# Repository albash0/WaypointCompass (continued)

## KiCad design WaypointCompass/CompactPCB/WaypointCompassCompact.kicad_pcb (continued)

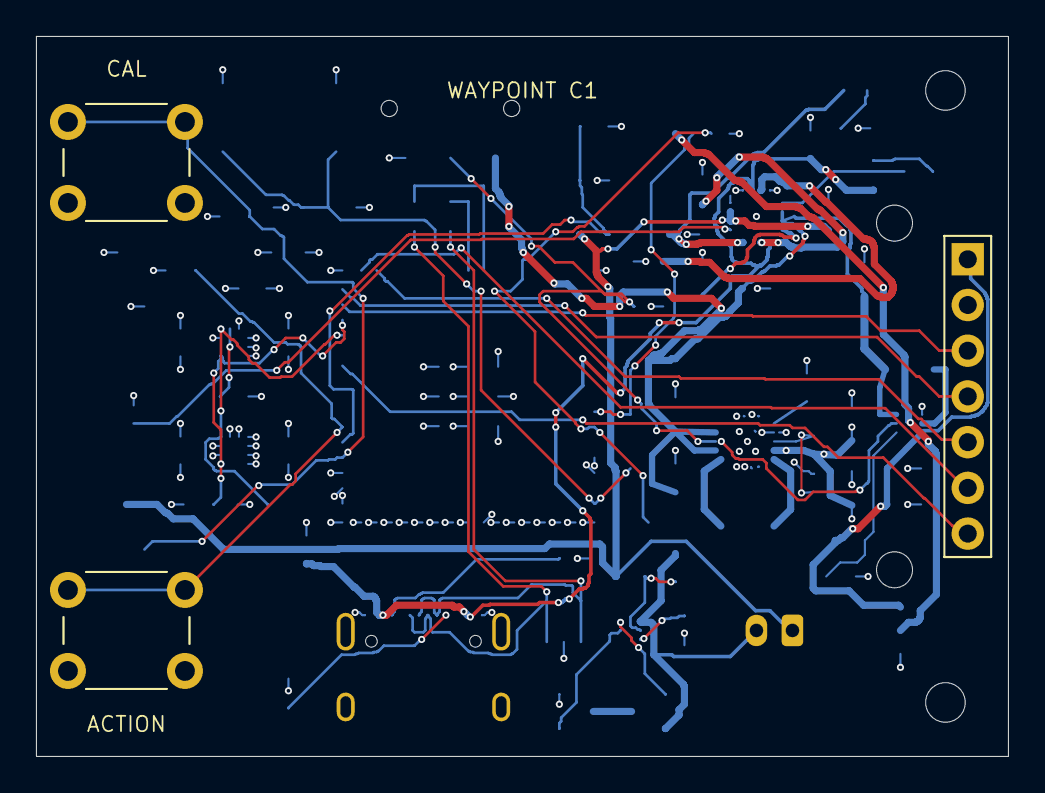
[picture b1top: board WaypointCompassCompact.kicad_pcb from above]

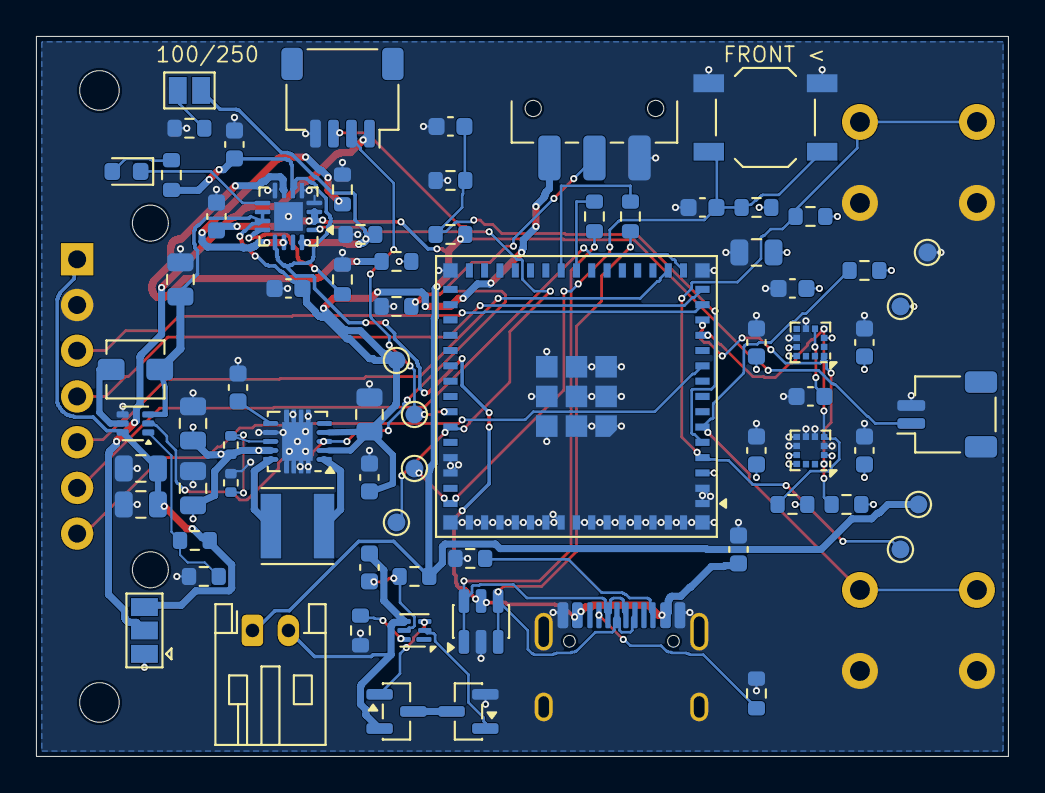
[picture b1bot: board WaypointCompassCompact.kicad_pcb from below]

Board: 4 copper layers, 54.0 x 40.0 mm, 82 parts (75 on the bottom side), 48 nets.

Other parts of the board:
H1, H2, H3, H4: MOUNT

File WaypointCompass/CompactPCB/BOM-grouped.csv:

References,Quantity,MPN,Value,Footprint,Assembly,Notes
U1,1,ESP32-S3-MINI-1U-N4R2,ESP32-S3-MINI-1U-N4R2,RF_Module:ESP32-S2-MINI-1U,Rear SMT,Optional external 2.4 GHz antenna; no RF used by compass firmware
U2,1,LIS2DH12TR,LIS2DH12TR,Package_LGA:LGA-12_2x2mm_P0.5mm,Rear SMT,I2C 0x18; +X must be mapped to device front
U3,1,LIS2MDLTR,LIS2MDLTR,Package_LGA:LGA-12_2x2mm_P0.5mm,Rear SMT,I2C 0x1E; NC pins 2/11/12 left open
U4,1,BQ24074RGTR,BQ24074RGTR,Package_DFN_QFN:VQFN-16-1EP_3x3mm_P0.5mm_EP1.6x1.6mm,Rear SMT,4.2 V single-cell; fixed 500 mA USB input mode; 100 mA default charge
U5,1,TPS63060DSCR,TPS63060DSCR,Package_SON:Texas_S-PWSON-N10,Rear SMT,3.3 V buck-boost; forced PWM for predictable sensor noise
U6,1,TPS61023DRLR,TPS61023DRLR,Package_TO_SOT_SMD:SOT-563,Rear SMT,5 V GPS breakout supply while running from battery
U7,1,BQ29700DSET,BQ29700DSET,Package_SON:WSON-6_1.5x1.5mm_P0.5mm,Rear SMT,4.275 V / 2.8 V cell protection; cell negative isolated from system GND
Q1,1,AO3400A,AO3400A,Package_TO_SOT_SMD:SOT-23,Rear SMT,Discharge FET; common drain with Q2
Q2,1,AO3400A,AO3400A,Package_TO_SOT_SMD:SOT-23,Rear SMT,Charge FET; common drain with Q1
U8,1,USBLC6-2SC6,USBLC6-2SC6,Package_TO_SOT_SMD:SOT-23-6,Rear SMT,USB ESD diode array placed near connector
J1,1,TYPE-C-31-M-12,USB-C USB2,Connector_USB:USB_C_Receptacle_HRO_TYPE-C-31-M-12,Rear SMT + shell through-hole,USB device; use a 5 V USB source capable of 500 mA
J2,1,Existing 7-pin GC9A01 TFT + straight 2.54 mm header,GC9A01 TFT,CompassCarrier:GC9A01_TFT_Socket,Front through-hole / manual,"Screen centered (27,20); 2.54 mm straight-header spacer; 5 V supply as on working prototype"
J3,1,S2B-PH-K-S(LF)(SN),BATTERY JST-PH2,Connector_JST:JST_PH_S2B-PH-K_1x02_P2.00mm_Horizontal,Rear through-hole,Pin 1 positive; 300-1000 mAh 1S 4.2 V-charge Li-ion/LiPo; verify plug polarity
J4,1,SM04B-SRSS-TB(LF)(SN),GPS JST-SH4,Connector_JST:JST_SH_SM04B-SRSS-TB_1x04-1MP_P1.00mm_Horizontal,Rear SMT,"New SH cable: VCC,RX,TX,GND; UART is 3.3 V"
J5,1,SM02B-SRSS-TB(LF)(SN),BATTERY NTC,Connector_JST:JST_SH_SM02B-SRSS-TB_1x02-1MP_P1.00mm_Horizontal,Rear SMT,External 10k 103AT-2 thermistor attached to cell; no NTC = charge inhibited
SW1,1,B3F-1000,CAL/BOOT,Button_Switch_THT:SW_PUSH_6mm,Front through-hole / manual,"Body center (5,7); GPIO0 held on reset enters ROM bootloader"
SW2,1,B3F-1000,ACTION,Button_Switch_THT:SW_PUSH_6mm,Front through-hole / manual,"Body center (5,33); GPIO2"
SW3,1,TL3342F160QG,RESET,Button_Switch_SMD:SW_SPST_TL3342,Rear SMT,Rear reset button
SW4,1,JS102011SAQN,POWER,Button_Switch_SMD:SW_SPDT_CK_JS102011SAQN,Rear SMT,Off grounds regulator enable; charger stays active
"R1, R2",2,RC0603FR-074K7L,4.7k,Resistor_SMD:R_0603_1608Metric,Rear SMT,"1%, 0603; "
"C1, C3, C8, C9, C10, C15, C18, C22",8,GRM188R71C104KA01D,100n,Capacitor_SMD:C_0603_1608Metric,Rear SMT,"100 nF, 16 V, X7R, 0603"
"C2, C4, C6, C11",4,GRM188R71A105KA61D,1u,Capacitor_SMD:C_0603_1608Metric,Rear SMT,"1 uF, 10 V, X7R, 0603"
C5,1,GRM188R71C224KA01D,220n,Capacitor_SMD:C_0603_1608Metric,Rear SMT,"220 nF, 16 V, X7R, 0603"
"R3, R4, R5, R17",4,RC0603FR-0710KL,10k,Resistor_SMD:R_0603_1608Metric,Rear SMT,"1%, 0603; "
"C7, C14, C19",3,GRM21BR61A106KE19L,10u,Capacitor_SMD:C_0805_2012Metric,Rear SMT,"10 uF, 10 V, X5R, 0805"
"R6, R7",2,RC0603FR-0722RL,22,Resistor_SMD:R_0603_1608Metric,Rear SMT,"1%, 0603; "
"R8, R9",2,RC0603FR-075K1L,5.1k,Resistor_SMD:R_0603_1608Metric,Rear SMT,"1%, 0603; "
R10,1,RC0603FR-07330KL,330k,Resistor_SMD:R_0603_1608Metric,Rear SMT,"1%, 0603; "
"R11, R18, R22",3,RC0603FR-07100KL,100k,Resistor_SMD:R_0603_1608Metric,Rear SMT,"1%, 0603; "
R12,1,RC0603FR-078K87L,8.87k,Resistor_SMD:R_0603_1608Metric,Rear SMT,"1%, 0603; "
R13,1,RC0603FR-075K9L,5.90k,Resistor_SMD:R_0603_1608Metric,Rear SMT,"1%, 0603; "
R14,1,RC0603FR-073K16L,3.16k,Resistor_SMD:R_0603_1608Metric,Rear SMT,"1%, 0603; ILIM unused in fixed USB500 mode; populated for defined pin bias"
R15,1,RC0603FR-0771K5L,71.5k,Resistor_SMD:R_0603_1608Metric,Rear SMT,"1%, 0603; 9.53 h typical timer; 7.15-11.92 h factor limits; 1000 mAh use 250 mA mode"
"C12, C13",2,GRM188R61A475KE15D,4.7u,Capacitor_SMD:C_0603_1608Metric,Rear SMT,"4.7 uF, 10 V, X5R, 0603"
"R16, R24",2,RC0603FR-072K2L,2.2k,Resistor_SMD:R_0603_1608Metric,Rear SMT,"1%, 0603; "
D1,1,LTST-C190KFKT,CHARGE amber,LED_SMD:LED_0603_1608Metric,Rear SMT,Charge active / fault indicator
L1,1,IFSC1515AHER1R5M01,1.5uH >=3A,Inductor_SMD:L_Vishay_IFSC-1515AH_4x4x1.8mm,Rear SMT,Vishay shielded 1.5 uH; 3.60 A nominal saturation current; 4 x 4 mm
"C16, C17, C20, C21",4,C2012X5R1A226M125AB,22u,Capacitor_SMD:C_0805_2012Metric,Rear SMT,"22 uF, 10 V, X5R, 0805"
R19,1,RC0402FR-07560KL,560k,Resistor_SMD:R_0402_1005Metric,Rear SMT,"1%, 0402; "
R20,1,RC0402FR-07100KL,100k,Resistor_SMD:R_0402_1005Metric,Rear SMT,"1%, 0402; "
L2,1,IHLP1212BZEV1R0M01,1uH >=2A,Inductor_SMD:L_Vishay_IHLP-1212,Rear SMT,Vishay shielded 1 uH IHLP-1212BZ-01; 6.92 A typical saturation; 4.99 A typical thermal rating
R21,1,RC0603FR-07732KL,732k,Resistor_SMD:R_0603_1608Metric,Rear SMT,"1%, 0603; "
R23,1,RC0603FR-07330RL,330,Resistor_SMD:R_0603_1608Metric,Rear SMT,"1%, 0603; "

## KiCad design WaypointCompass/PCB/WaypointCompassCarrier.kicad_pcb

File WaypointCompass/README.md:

# Waypoint Compass / Bottle Radar

The ESP32 selects the closest of **19 retail liquor stores** from the City of Boulder's public liquor-license map, using the current GPS position. It runs offline: no Wi-Fi, account, phone or API key is needed.

## Screen

- Mint-and-gold arrow, rotating north/cardinal markers and a large distance readout.
- Store name and left/right turn cue; north-up fallback when neither magnetometer heading nor GPS course is available.
- Animated GPS radar while acquiring a fix. No target arrow is shown with a stale or missing fix.
- Animated bottle calibration screen and a "FOUND IT!" celebration within 25 m of the destination's map point.
- Detailed GPS reception page with satellite counts, RX rate, NMEA checksums, SNR and HDOP.

Distances are **straight-line**, not walking routes. The nearest candidate is reevaluated once per second, so the target can change as you move. Store coordinates are city GIS points, not surveyed entrances. The embedded list is a **2026-10-16 snapshot**; opening hours and live closures are not checked. Grocery beer/wine licenses and bars are excluded; the list uses the city's `Retail Liquor Store` class with `STATUS=1`.

## Firmware variants

- `WaypointCompass.ino`: the working SuperMini + QMC5883P GY-271 + MPU6050 GY-521 prototype. The TFT's CS is tied to GND and RST to 3V3, matching its existing running sketch. SCK=10, MOSI=11, DC=13; GPS RX=44/TX=43; I2C SDA=8/SCL=9. GY-271 remains on the GY-521 auxiliary I2C bus with bypass enabled.
- `CompactPCB/firmware/WaypointCompassCompact/WaypointCompassCompact.ino`: the C1 PCB with LIS2MDL/LIS2DH12 and TFT CS=12/RST=6. QSPI PSRAM enabled for its ESP32-S3-MINI-1U-N4R2.

Both variants use the same `BoulderStores.h`, `BottleNavigation.h` and `BottleUI.h`. Their sensor setup, pin configuration, tilt compensation and saved calibration stay specific to their hardware. Keep the copied headers synchronized when editing either firmware.

## Upload and controls

Use ESP32S3 Dev Module, ESP32 Arduino core 3.3.8, 4 MB flash, Hardware CDC/JTAG USB mode and USB CDC On Boot enabled. Install TinyGPSPlus, Adafruit GFX and Adafruit GC9A01A with their dependencies. The prototype does not require PSRAM; C1 uses QSPI PSRAM.

BOOT/CAL starts a 10-second calibration. Roll, pitch and turn the assembled device around all axes; accepted calibration survives resets. The C1 ACTION button toggles detailed diagnostics. Serial Monitor uses 115200 baud with newline endings:

| Command | Action |
| --- | --- |
| `NEAREST` | Enable automatic nearest-store mode; saved across resets. This is the default for the new firmware. |
| `STORES` | Print the embedded store names, addresses and coordinates. |
| `DETAILS` | Toggle the detailed GPS screen. |
| `STATUS` | Report navigation mode, selected store, GPS and sensor status. |
| `CAL` | Start 10-second 3D calibration. |
| `NMEA` | Print five seconds of raw GPS data. |
| `latitude,longitude` | Save a manual waypoint and switch to manual mode. |
| `CLEAR` | Clear the manual target and disable automatic mode. Use NEAREST to resume. |

The old manual waypoint is ignored while automatic mode is active; calibration is retained. Automatic target updates do not write GPS positions to flash.

## Store data and checks

[City liquor-license map](https://maps.bouldercolorado.gov/liquor-licenses/) is linked from the [City licensing page](https://bouldercolorado.gov/services/liquor-licenses). The exact query and records are stored in `data/boulder-stores.json`.

To refresh the list, run `python3 tools/update_store_list.py` with internet access. It queries the city GIS, rejects missing/out-of-area coordinates and regenerates the header in both sketch folders. Recompile and upload afterward. Review business names/status when refreshing.

`tests/run_tests.sh` checks nearest-store selection, missing/stale fixes and geographic distance edge cases under address/undefined-behavior sanitizers. It also renders eight screens with the actual Adafruit GFX implementation for visual inspection. `preview/` contains sample UI images, not live measurements.

Personal waypoints and device backups are excluded from the public source export. Both compiled manual destination defaults are unset (`NAN`). Public city-listed business coordinates remain in the offline dataset.

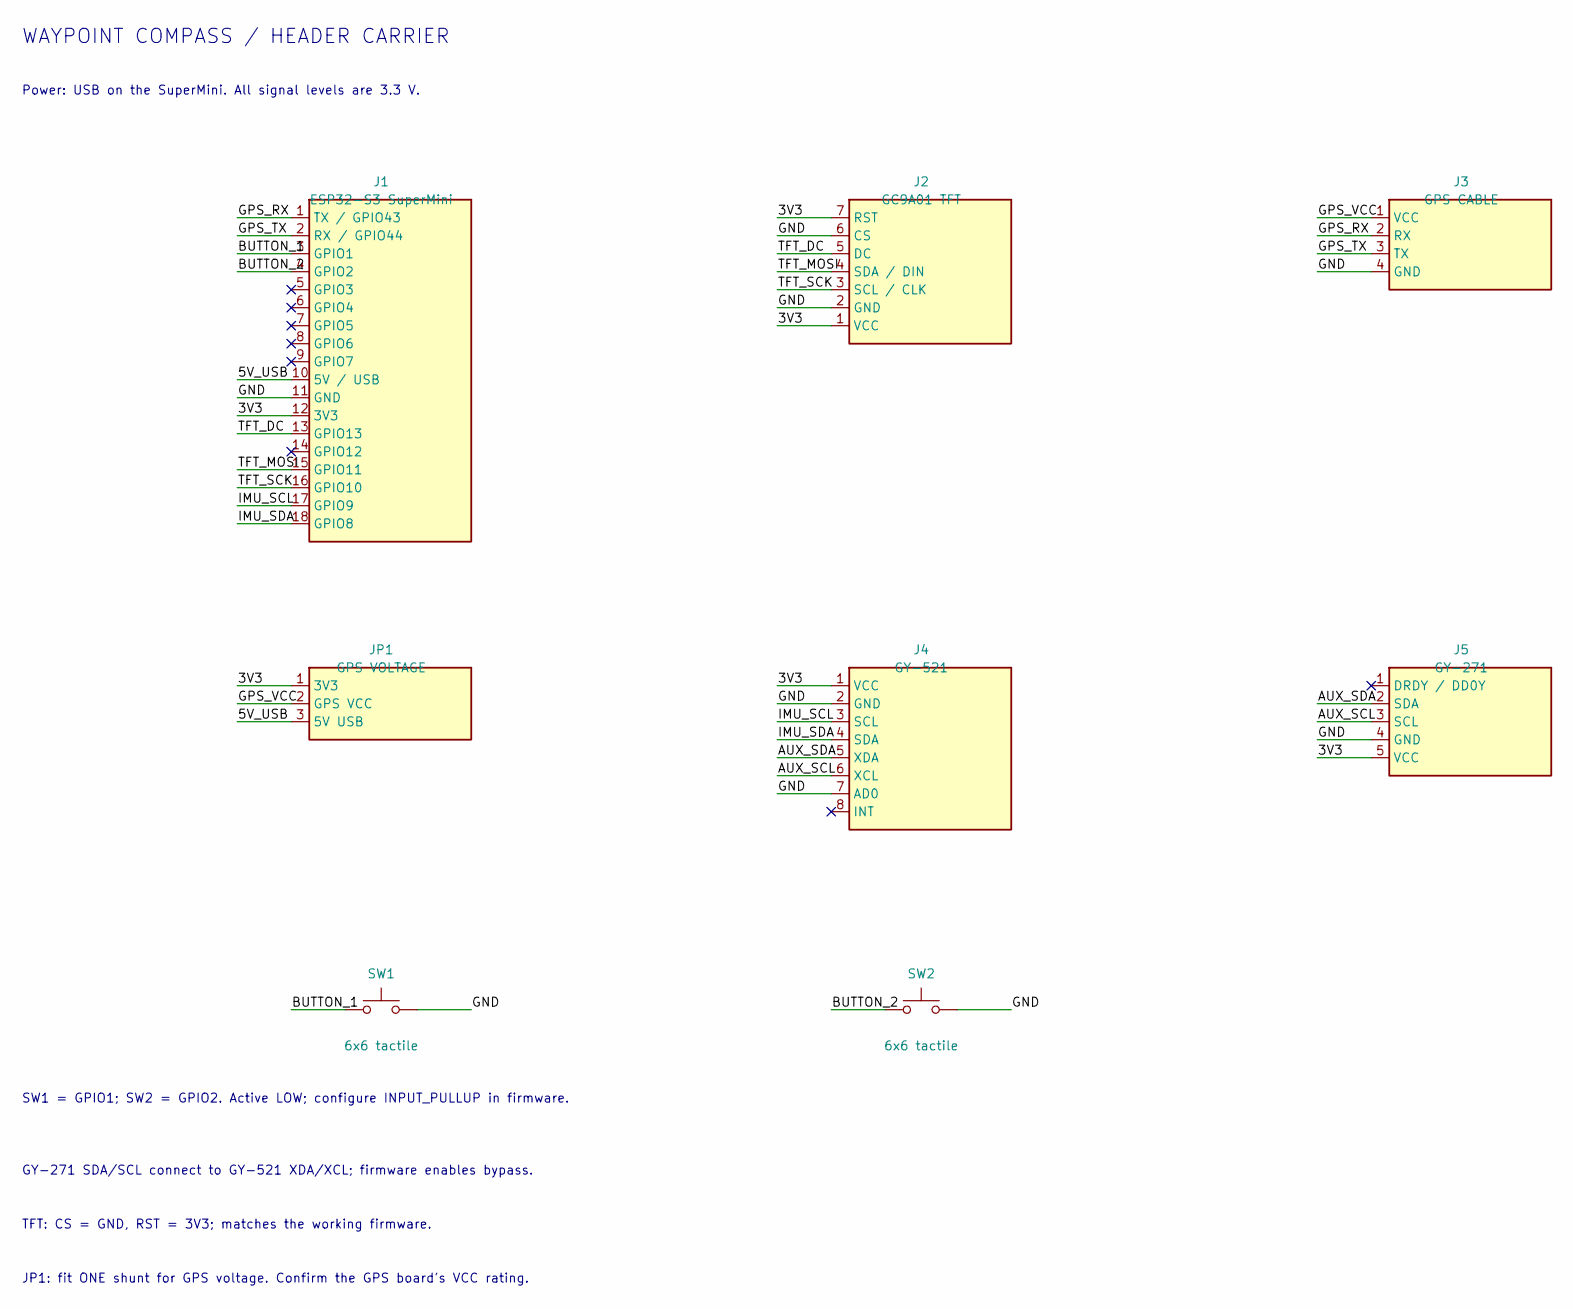
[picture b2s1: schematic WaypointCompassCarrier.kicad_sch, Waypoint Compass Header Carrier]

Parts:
J1: ESP32-S3 SuperMini; ESP32_S3_SuperMini_2x09_Sockets
J2: GC9A01 TFT; GC9A01_TFT_Socket
J3: GPS CABLE; GPS_CABLE_Socket
J4: GY-521; GY_521_Socket
J5: GY-271; GY_271_Socket
JP1: GPS VOLTAGE; GPS_VOLTAGE_Socket
SW1, SW2: 6x6 tactile; SW_PUSH_6mm

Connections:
/3V3: J1.12 (3V3), J2.1 (VCC), J2.7 (RST), J4.1 (VCC), J5.5 (VCC), JP1.1 (3V3)
/5V_USB: J1.10 (5V / USB), JP1.3 (5V USB)
/AUX_SCL: J4.6 (XCL), J5.3 (SCL)
/AUX_SDA: J4.5 (XDA), J5.2 (SDA)
/BUTTON_1: J1.3 (GPIO1), SW1.1
/BUTTON_2: J1.4 (GPIO2), SW2.1
/GND: J1.11 (GND), J2.2 (GND), J2.6 (CS), J3.4 (GND), J4.2 (GND), J4.7 (AD0), J5.4 (GND), SW1.2, SW2.2
/GPS_RX: J1.1 (TX / GPIO43), J3.2 (RX)
/GPS_TX: J1.2 (RX / GPIO44), J3.3 (TX)
/GPS_VCC: J3.1 (VCC), JP1.2 (GPS VCC)
/IMU_SCL: J1.17 (GPIO9), J4.3 (SCL)
/IMU_SDA: J1.18 (GPIO8), J4.4 (SDA)
/TFT_DC: J1.13 (GPIO13), J2.5 (DC)
/TFT_MOSI: J1.15 (GPIO11), J2.4 (SDA / DIN)
/TFT_SCK: J1.16 (GPIO10), J2.3 (SCL / CLK)

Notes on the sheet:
WAYPOINT COMPASS / HEADER CARRIER
Power: USB on the SuperMini. All signal levels are 3.3 V.
GY-271 SDA/SCL connect to GY-521 XDA/XCL; firmware enables bypass.
TFT: CS = GND, RST = 3V3; matches the working firmware.
JP1: fit ONE shunt for GPS voltage. Confirm the GPS board's VCC rating.
SW1 = GPIO1; SW2 = GPIO2. Active LOW; configure INPUT_PULLUP in firmware.

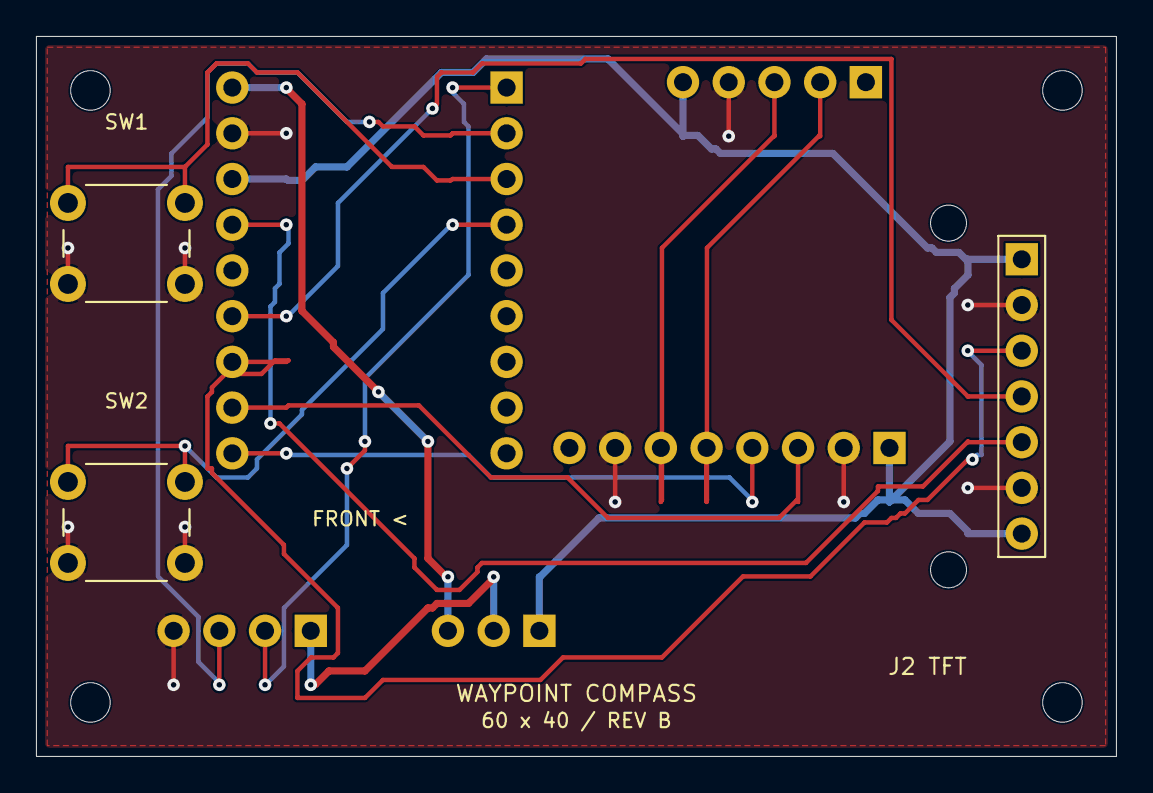
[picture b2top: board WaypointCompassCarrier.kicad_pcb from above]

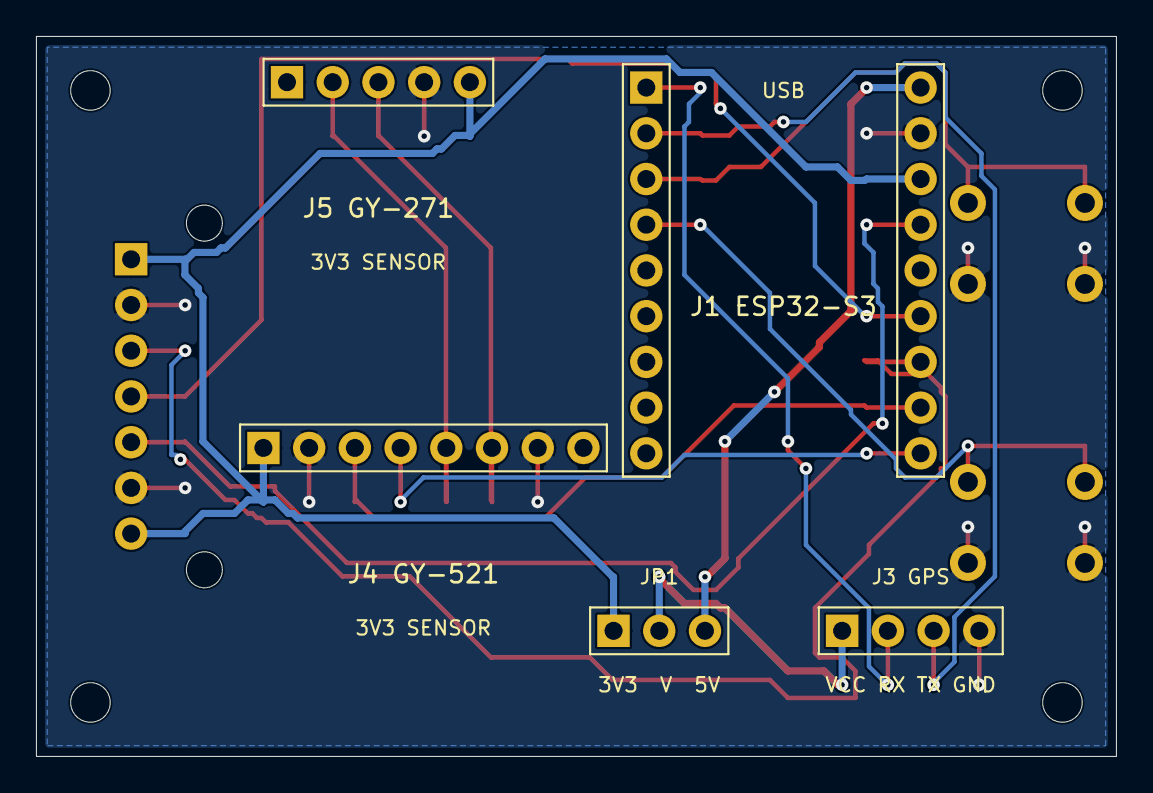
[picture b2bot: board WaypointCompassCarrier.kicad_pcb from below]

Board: 2 copper layers, 60.0 x 40.0 mm, 14 parts (5 on the bottom side), 15 nets.

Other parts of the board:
H1, H2, H3, H4: MountingHole_2.2mm; MountingHole_2.2mm_Carrier
H5, H6: MountingHole_2.0mm; MountingHole_2.0mm_Carrier

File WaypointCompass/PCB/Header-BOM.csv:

Reference,Quantity,Description,Pitch_mm,Side,Notes
J1,2,Male header 1x9 straight,2.54,Back,15.24 mm row spacing; solder to both boards; 2.54 mm PCB gap
J2,1,Male header 1x7 straight,2.54,Front,Direct solder; 2.54 mm gap; GC9A01 TFT; RST CS DC SDA SCL GND VCC
J3,1,Male header 1x4 straight,2.54,Back,GPS cable; VCC RX TX GND
J4,1,Male header 1x8 straight,2.54,Back,Direct solder; 2.54 mm gap; GY-521; VCC GND SCL SDA XDA XCL AD0 INT
J5,1,Male header 1x5 straight,2.54,Back,Direct solder; 2.54 mm gap; GY-271; DRDY SDA SCL GND VCC
JP1,1,Male header 1x3 straight,2.54,Back,GPS voltage selector
JP1,1,Jumper shunt 2-pin,2.54,Back,Select exactly one GPS supply
SW1 SW2,2,Standard 6x6 mm through-hole tactile pushbutton,,Front,Four leads on 6.50 x 4.50 mm spacing; normally open; short actuator
J3 cable,1,Four-wire female header cable,2.54,Off-board,Wire to GPS VCC RX TX GND
H1 H2 H3 H4,4,Optional M2 nonmagnetic case fasteners,,Both,2.20 mm carrier holes
H5 H6,2,Optional M1.6 nonmagnetic TFT supports,,Front,2.00 mm holes; 2.54 mm facing-PCB gap

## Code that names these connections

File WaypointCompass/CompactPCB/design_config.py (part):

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add('U1','ESP32-S3-MINI-1U-N4R2','RF_Module:ESP32-S3-MINI-1U','RF_Module:ESP32-S2-MINI-1U',mcu,[24,20],mpn='ESP32-S3-MINI-1U-N4R2',note='Optional external 2.4 GHz antenna; no RF used by compass firmware')
accel=custompins([(1,'SCL','input'),(2,'CS','input'),(3,'SA0','input'),(4,'SDA','bidirectional'),(5,'RES_GND','passive'),(6,'GND','power_in'),(7,'GND','passive'),(8,'GND','passive'),(9,'VDD','power_in'),(10,'VDD_IO','power_in'),(11,'INT2','output'),(12,'INT1','output')])
add('U2','LIS2DH12TR',None,'Package_LGA:LGA-12_2x2mm_P0.5mm',{1:'I2C_SCL',2:'3V3',3:'GND',4:'I2C_SDA',5:'GND',6:'GND',7:'GND',8:'GND',9:'3V3',10:'3V3'},[11,23],custom=accel,note='I2C 0x18; +X must be mapped to device front')
add('U3','LIS2MDLTR','Sensor_Magnetic:LIS2MDL','Package_LGA:LGA-12_2x2mm_P0.5mm',{1:'I2C_SCL',3:'3V3',4:'I2C_SDA',5:'MAG_C1',6:'GND',8:'GND',9:'3V3',10:'3V3'},[11,17],note='I2C 0x1E; NC pins 2/11/12 left open')
# Power path: VBUS -> charger -> SYS -> 3.3 V buck-boost / 5 V GPS boost.
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add('U5','TPS63060DSCR','Regulator_Switching:TPS63060','Package_SON:Texas_S-PWSON-N10',{1:'BB_L1',2:'SYS',3:'POWER_EN',4:'SYS',6:'BB_AUX',7:'GND',8:'BB_FB',9:'3V3',10:'BB_L2',11:'GND'},[41,20],note='3.3 V buck-boost; forced PWM for predictable sensor noise')
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add('Q1','AO3400A','Transistor_FET:AO3400A','Package_TO_SOT_SMD:SOT-23',{1:'PROT_DOUT',2:'CELL_NEG',3:'FET_MID'},[33,36],180,note='Discharge FET; common drain with Q2')
add('Q2','AO3400A','Transistor_FET:AO3400A','Package_TO_SOT_SMD:SOT-23',{1:'PROT_COUT',2:'GND',3:'FET_MID'},[29,36],note='Charge FET; common drain with Q1')
add('U8','USBLC6-2SC6','Power_Protection:USBLC6-2SC6','Package_TO_SOT_SMD:SOT-23-6',{1:'USB_M',2:'GND',3:'USB_P',4:'USB_P',5:'VBUS',6:'USB_M'},[20,31],note='USB ESD diode array placed near connector')
usb={p['number']:('GND' if p['name'] in ('GND','SHIELD') else 'VBUS' if p['name']=='VBUS' else 'USB_P' if p['name']=='D+' else 'USB_M' if p['name']=='D-' else p['name'] if p['name'] in ('CC1','CC2') else None) for p in pins(symbol('Connector','USB_C_Receptacle_USB2.0_16P'))}
add('J1','USB-C USB2','Connector:USB_C_Receptacle_USB2.0_16P','Connector_USB:USB_C_Receptacle_HRO_TYPE-C-31-M-12',usb,[20,38],note='USB device; use a 5 V USB source capable of 500 mA')
# Front TFT landing reused; keep the cheap existing display module.
tftp=custompins([(1,'VCC','power_in'),(2,'GND','power_in'),(3,'SCL','input'),(4,'SDA','input'),(5,'DC','input'),(6,'CS','input'),(7,'RST','input')])
add('J2','GC9A01 TFT',None,'CompassCarrier:GC9A01_TFT_Socket',{1:'GPS_5V',2:'GND',3:'TFT_SCK',4:'TFT_MOSI',5:'TFT_DC',6:'TFT_CS',7:'TFT_RST'},[51.74,20],90,'front',custom=tftp,note='Screen centered (27,20); 2.54 mm straight-header spacer; 5 V supply as on working prototype')
add('J3','BATTERY JST-PH2','Connector_Generic:Conn_01x02','Connector_JST:JST_PH_S2B-PH-K_1x02_P2.00mm_Horizontal',{1:'VBAT',2:'CELL_NEG'},[39,37],note='Pin 1 positive; 300-1000 mAh 1S 4.2 V-charge Li-ion/LiPo; verify plug polarity')
add('J4','GPS JST-SH4','Connector_Generic:Conn_01x04','Connector_JST:JST_SH_SM04B-SRSS-TB_1x04-1MP_P1.00mm_Horizontal',{1:'GPS_VCC',2:'GPS_RX',3:'GPS_TX',4:'GND'},[50,20],90,note='New SH cable: VCC,RX,TX,GND; UART is 3.3 V')
add('J5','BATTERY NTC','Connector_Generic:Conn_01x02','Connector_JST:JST_SH_SM02B-SRSS-TB_1x02-1MP_P1.00mm_Horizontal',{1:'BAT_TS',2:'GND'},[49,35],note='External 10k 103AT-2 thermistor attached to cell; no NTC = charge inhibited')
add('JP1','GPS 3V3/5V','Jumper:Jumper_3_Open','Jumper:SolderJumper-3_P1.3mm_Open_Pad1.0x1.5mm',{1:'3V3',2:'GPS_VCC',3:'GPS_5V'},[48,24],90,note='Bridge 2-3 by default for 5 V breakout; never bridge both sides')
add('JP2','FAST 250mA','Jumper:Jumper_2_Open','Jumper:SolderJumper-2_P1.3mm_Open_Pad1.0x1.5mm',{1:'CHG_ISET',2:'FAST_R'},[40,3],note='Open=100 mA for 300-500 mAh; bridge=250 mA for 500-1000 mAh cells rated for it')
add('SW1','CAL/BOOT','Switch:SW_Push','Button_Switch_THT:SW_PUSH_6mm',{1:'BOOT',2:'GND'},[1.75,4.75],side='front',note='Body center (5,7); GPIO0 held on reset enters ROM bootloader')
add('SW2','ACTION','Switch:SW_Push','Button_Switch_THT:SW_PUSH_6mm',{1:'BUTTON_2',2:'GND'},[1.75,30.75],side='front',note='Body center (5,33); GPIO2')
add('SW3','RESET','Switch:SW_Push','Button_Switch_SMD:SW_SPST_TL3342',{1:'MCU_EN',2:'GND'},[10,29],note='Rear reset button')
add('SW4','POWER','Switch:SW_SPDT','Button_Switch_SMD:SW_SPDT_CK_JS102011SAQN',{1:'GND',2:'POWER_EN',3:'SYS'},[49,8],90,note='Off grounds regulator enable; charger stays active')
# Sensor and MCU support.
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r('R10','330k','VBAT','BAT_ADC',[31,11]);r('R11','100k','BAT_ADC','GND',[31,8]);c('C10','100n','BAT_ADC','GND',[31,5])
# Charger: 890/8870 = 100.3 mA nominal. Parallel 5.90k selects 251 mA.
r('R12','8.87k','CHG_ISET','GND',[37,5]);r('R13','5.90k','FAST_R','GND',[43,3])
r('R14','3.16k','CHG_ILIM','GND',[36,11],90,note='ILIM unused in fixed USB500 mode; populated for defined pin bias')
r('R15','71.5k','CHG_TMR','GND',[37,8],90,note='9.53 h typical timer; 7.15-11.92 h factor limits; 1000 mAh use 250 mA mode')
c('C11','1u','VBUS','GND',[43,6],90);c('C12','4.7u','VBAT','GND',[44,10],90);c('C13','4.7u','SYS','GND',[40,13])
r('R16','2.2k','VBUS','LED_CHG_A',[47,12]);add('D1','CHARGE amber','Device:LED','LED_SMD:LED_0603_1608Metric',{1:'CHG_N',2:'LED_CHG_A'},[50,12],note='Charge active / fault indicator')
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
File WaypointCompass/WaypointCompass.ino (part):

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#include "BottleUI.h"

// ESP32-S3 SuperMini pins. Change these if your particular board labels differ.
constexpr int GPS_RX = 44;  // ESP32 RX pad <- GPS TX
constexpr int GPS_TX = 43;  // ESP32 TX pad -> GPS RX (optional)
constexpr int TFT_SCK = 10; // Display SCL/CLK; this is SPI, not I2C
constexpr int TFT_MOSI = 11;// Display SDA/DIN; this is SPI, not I2C
constexpr int TFT_CS = -1; // TFT CS tied to GND; GPIO12 is not used.
constexpr int TFT_DC = 13;
constexpr int TFT_RST = -1; // TFT RST/RES tied to 3V3.
constexpr int MAG_SDA = 8;
constexpr int MAG_SCL = 9;
constexpr uint8_t MAG_ADDRESS = 0x2C; // Verified QMC5883P GY-271
// GY-521/MPU-6050 sits on GPIO8/9. Its XDA/XCL pins carry the GY-271
// after I2C bypass is enabled. These signs assume matching X/Y board axes.
constexpr float IMU_X_SIGN = 1.0f;
constexpr float IMU_Y_SIGN = 1.0f;
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
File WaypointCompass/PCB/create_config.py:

"""Module header pin maps and placement. Coordinates in millimeters."""
import json
from pathlib import Path


def row(ref, value, names, nets, xy, schematic, side="back", body=None):
    n = len(names)
    lo, hi = -(n - 1) * 1.27, (n - 1) * 1.27
    module = {
        "ref": ref, "value": value,
        "footprint": value.replace("-", "_").replace(" ", "_") + "_Socket",
        "side": side, "pcb_at": xy, "schematic_at": schematic,
        "pins": [{"number": str(i + 1), "name": name, "net": net,
                  "at": [round(lo + 2.54 * i, 3), 0]}
                 for i, (name, net) in enumerate(zip(names, nets))],
        "courtyard": [round(lo - 1.6, 3), -1.7, round(hi + 1.6, 3), 1.7],
        "socket_outlines": [[round(lo - 1.3, 3), -1.3, round(hi + 1.3, 3), 1.3]],
        "ref_at": [0, -3],
        "labels": [[ref + " " + value, 0, 4, 0.9]],
    }
    if body:
        module["body"] = body
    return module


espnames = (["TX / GPIO43", "RX / GPIO44"] + ["GPIO" + str(i) for i in range(1, 8)]
            + ["5V / USB", "GND", "3V3", "GPIO13", "GPIO12", "GPIO11", "GPIO10", "GPIO9", "GPIO8"])
espnets = (["GPS_RX", "GPS_TX", "BUTTON_1", "BUTTON_2"] + [None] * 5
           + ["5V_USB", "GND", "3V3", "TFT_DC", None, "TFT_MOSI", "TFT_SCK", "IMU_SCL", "IMU_SDA"])
esp = {
    "ref": "J1", "value": "ESP32-S3 SuperMini",
    "footprint": "ESP32_S3_SuperMini_2x09_Sockets", "side": "back",
    "pcb_at": [118.5, 113], "schematic_at": [76.2, 40.64],
    "pins": [{"number": str(i + 1), "name": name, "net": espnets[i],
              "at": [-7.62 if i < 9 else 7.62, round(-10.16 + (i % 9) * 2.54, 3)]}
             for i, name in enumerate(espnames)],
    "courtyard": [-9.25, -12.1, 9.25, 12.1],
    "socket_outlines": [[-8.92, -11.46, -6.32, 11.46], [6.32, -11.46, 8.92, 11.46]],
    "body": [-9, -11.75, 9, 11.75], "ref_at": [0, 0],
    "labels": [["USB", 0, -10, 0.8], ["J1 ESP32-S3", 0, 2, 1]],
}
tft = row("J2", "GC9A01 TFT", ["RST", "CS", "DC", "SDA / DIN", "SCL / CLK", "GND", "VCC"],
          ["3V3", "GND", "TFT_DC", "TFT_MOSI", "TFT_SCK", "GND", "3V3"],
          [154.74, 120], [152.4, 40.64], side="front", body=[-19, -43.74, 19, 1.76])
tft["rotation"] = 90
for i,pin in enumerate(tft["pins"]):
    pin["number"] = str(7-i)  # The supplied drawing marks VCC as pin 1.
tft["circles"] = [[0, -24.74, 19], [0, -24.74, 16.2]]
tft["labels"] = []
gps = row("J3", "GPS CABLE", ["VCC", "RX", "TX", "GND"],
          ["GPS_VCC", "GPS_RX", "GPS_TX", "GND"], [111.43, 133.02], [228.6, 40.64])
gps["labels"] = [["J3 GPS", 0, -3, 0.8], ["VCC RX TX GND", 0, 3, 0.8]]
imu = row("J4", "GY-521", ["VCC", "GND", "SCL", "SDA", "XDA", "XCL", "AD0", "INT"],
          ["3V3", "GND", "IMU_SCL", "IMU_SDA", "AUX_SDA", "AUX_SCL", "GND", None],
          [138.5, 122.86], [152.4, 106.68], body=[-10, 0, 10, 16])
imu["labels"] = [["J4 GY-521", 0, 7, 1], ["+X FRONT", 0, 10, 0.8]]
mag = row("J5", "GY-271", ["DRDY / DD0Y", "SDA", "SCL", "GND", "VCC"],
          [None, "AUX_SDA", "AUX_SCL", "GND", "3V3"], [141, 102.54], [228.6, 106.68],
          body=[-7.5, 0, 7.5, 18])
mag["labels"] = [["J5 GY-271", 0, 7, 1], ["+X FRONT", 0, 10, 0.8]]
jp = row("JP1", "GPS VOLTAGE", ["3V3", "GPS VCC", "5V USB"],
         ["3V3", "GPS_VCC", "5V_USB"], [125.4, 133.02], [76.2, 106.68])
jp["labels"] = [["JP1", 0, -3, 0.8], ["3V3  V  5V", 0, 3, 0.8]]
def button(ref, signal, center_y, schematic_x):
    return {
        "ref": ref, "value": "6x6 tactile", "kind": "button",
        "footprint": "SW_PUSH_6mm", "side": "front",
        "pcb_at": [101.75, center_y-2.25],
        "schematic_at": [schematic_x, 152.4],
        "pins": [{"number": "1", "name": signal, "net": signal},
                 {"number": "2", "name": "GND", "net": "GND"}],
        "physical_pads": [{"number": "1", "at": [0, 0]},
                          {"number": "1", "at": [6.5, 0]},
                          {"number": "2", "at": [0, 4.5]},
                          {"number": "2", "at": [6.5, 4.5]}],
        "labels": [[ref, 3.25, -4.5, 0.8]],
        "body_center": [105, center_y],
    }
sw1 = button("SW1", "BUTTON_1", 111.5, 76.2)
sw2 = button("SW2", "BUTTON_2", 127, 152.4)
config = {
    "status": "Header pin orders supplied by user; TFT dimensions from supplied module drawing; IMU/magnetometer body envelopes nominal",
    "board": [100, 100, 60, 40],
    "mounting_holes": [[103, 103], [157, 103], [103, 137], [157, 137]],
    "tft_holes": [[150.67, 110.37], [150.67, 129.63]],
    "modules": [esp, tft, gps, imu, mag, jp, sw1, sw2],
    "board_text": [["WAYPOINT COMPASS", 130, 136.5, 0.9], ["60 x 40 / REV B", 130, 138, 0.8],
                   ["J2 TFT", 149.5, 135, 0.9]],
}
Path(__file__).with_name("module_config.json").write_text(json.dumps(config, indent=2) + "\n")
